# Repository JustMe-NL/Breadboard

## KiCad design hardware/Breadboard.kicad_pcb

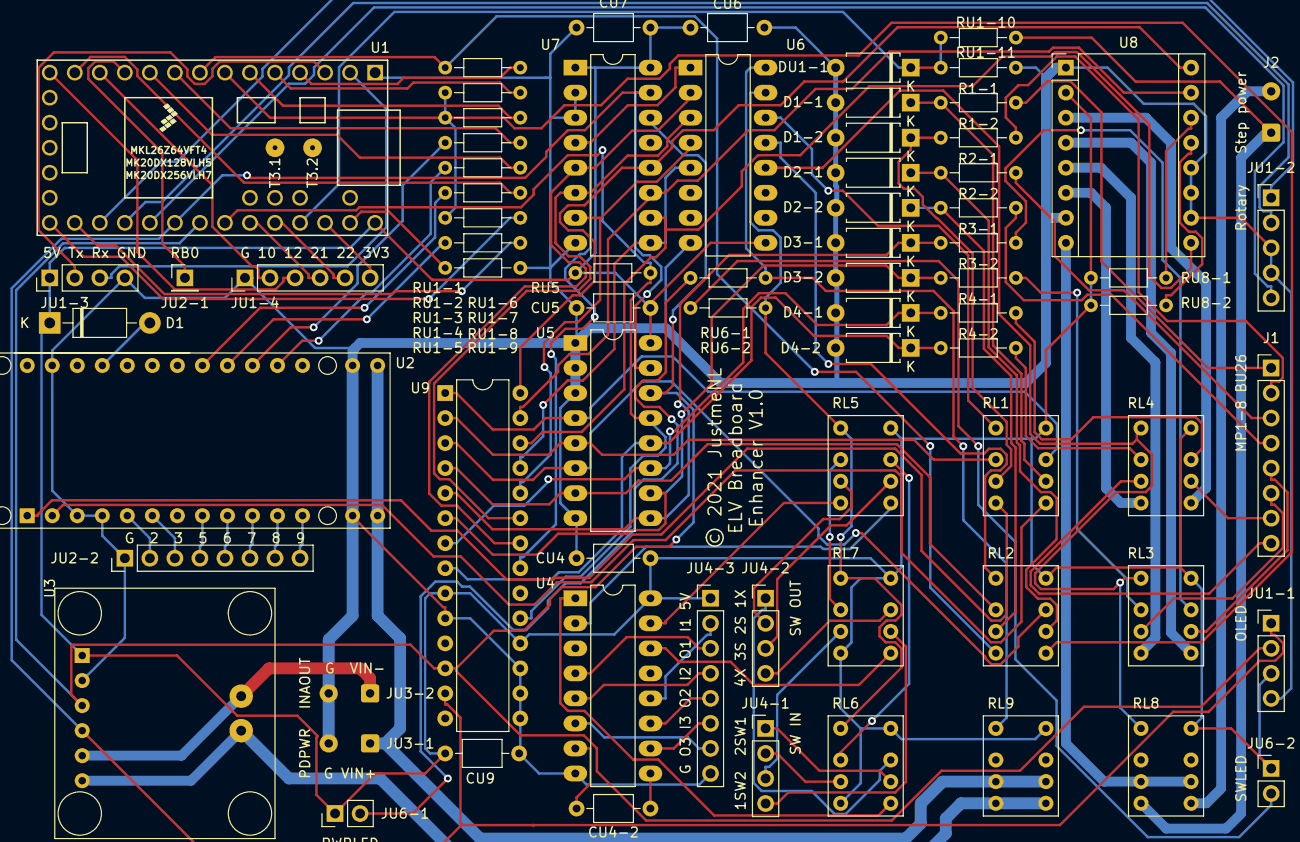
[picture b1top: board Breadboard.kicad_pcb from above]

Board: 2 copper layers, 73 parts (0 on the bottom side), 115 nets.

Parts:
CU4, CU5, CU6, CU7, CU9: C; C_Axial_L3.8mm_D2.6mm_P7.50mm_Horizontal
CU4-2: 100pF; C_Axial_L3.8mm_D2.6mm_P7.50mm_Horizontal
D1: 1N5819; D_DO-41_SOD81_P10.16mm_Horizontal
D1-1, D1-2, D2-1, D2-2, D3-1, D3-2, D4-1, D4-2: 1N4733A; D_A-405_P7.62mm_Horizontal
DU1-1: 1N4733A; D_A-405_P7.62mm_Horizontal
J1: 8PinBeardboard; PinHeader_1x08_P2.54mm_Vertical
J2: StepPower; SolderWire-0.25sqmm_1x02_P4.2mm_D0.65mm_OD1.7mm
JU1-1: OLED Display; PinHeader_1x04_P2.54mm_Vertical
JU1-2: Rotary Encoder; PinHeader_1x05_P2.54mm_Vertical
JU1-3: Serial; PinHeader_1x04_P2.54mm_Vertical
JU1-4: TeensySpare; PinHeader_1x06_P2.54mm_Vertical
JU2-1: PDSS/RB0; PinHeader_1x01_P2.54mm_Vertical
JU2-2, JU4-3: PS_Spare1; PinHeader_1x08_P2.54mm_Vertical
JU3-1: PD_Power; SolderWire-0.25sqmm_1x02_P4.2mm_D0.65mm_OD1.7mm
JU3-2: INA219; SolderWire-0.25sqmm_1x02_P4.2mm_D0.65mm_OD1.7mm
JU4-1: SW IN; PinHeader_1x04_P2.54mm_Vertical
JU4-2: SW OUT; PinHeader_1x04_P2.54mm_Vertical
JU6-1: PowerLED; PinHeader_1x02_P2.54mm_Vertical
JU6-2: SwitchLED; PinHeader_1x02_P2.54mm_Vertical
R1-1, R1-2, R2-1, R2-2, R3-1, R3-2, R4-1, R4-2: 1K; R_Axial_DIN0204_L3.6mm_D1.6mm_P7.62mm_Horizontal
RL1, RL2, RL3, RL4, RL5, RL6, RL7, RL8, RL9: HFD4-5
RU1-1, RU1-2: 2K2; R_Axial_DIN0204_L3.6mm_D1.6mm_P7.62mm_Horizontal
RU1-3: 4K7; R_Axial_DIN0204_L3.6mm_D1.6mm_P7.62mm_Horizontal
RU1-4, RU1-5, RU1-6, RU1-7, RU1-8: 100; R_Axial_DIN0204_L3.6mm_D1.6mm_P7.62mm_Horizontal
RU1-9: 0; R_Axial_DIN0204_L3.6mm_D1.6mm_P7.62mm_Horizontal
RU1-10: 10K; R_Axial_DIN0204_L3.6mm_D1.6mm_P7.62mm_Horizontal
RU1-11: 100K; R_Axial_DIN0204_L3.6mm_D1.6mm_P7.62mm_Horizontal
RU5, RU6-1, RU6-2, RU8-1, RU8-2: 1K; R_Axial_DIN0204_L3.6mm_D1.6mm_P7.62mm_Horizontal
U1: Teensy3.2; Teensy30_31_32_LC
U2: PD-Micro Module; PD_Micro
U3: INA219 Module
U4: MC14490; DIP-16_W7.62mm_LongPads
U5, U7: PCF8574; DIP-16_W7.62mm_LongPads
U6: ULN2003; DIP-16_W7.62mm_LongPads
U8: A4988 Module; Pololu_Breakout-16_15.2x20.3mm
U9: MCP23017_SP; DIP-28_W7.62mm

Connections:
+5V: CU4.1, CU5.1, CU6.1, CU7.1, CU9.1, D1.1, JU1-1.3, JU1-3.1, JU4-3.1, JU6-1.1, JU6-2.1, RL1.1, RL2.1, RL3.1, RL4.1, RL5.1, RL6.1, RL6.5, RL7.1, RL7.5, RL8.1, RL9.1, RU5.1, RU8-1.1, RU8-2.1, U1.33, U3.1, U4.16, U5.16, U6.9, U7.1, U7.16, U8.2, U9.9, U9.18
A1: RL3.4, U8.4
A2: RL3.5, U8.5
B1: RL4.4, U8.3
B2: RL4.5, U8.6
C_GPIO: U6.4, U7.7, U9.24
C_INT: RU5.2, U1.27, U5.13, U9.19
C_POWER: U6.1, U7.4, U9.21
C_SERIAL: U6.3, U7.6, U9.23
C_STEP: U6.5, U7.9, U9.25
C_SWITCH: U6.2, U7.5, U9.22
D5: RL2.4, RU1-2.1, RU1-3.1, RU1-7.1, U1.7
D6: RL2.5, RU1-1.1, U1.8
DBIN1: JU4-3.2, U4.12
DBIN2: JU4-3.4, U4.5
DBIN3: JU4-3.6, U4.10
DBOUT1: JU4-3.3, U4.4
DBOUT2: JU4-3.5, U4.11
DBOUT3: JU4-3.7, U4.6
EXP1: RL1.2, U5.4, U9.1
EXP2: RL1.7, U5.5, U9.2
EXP3: RL2.2, U5.6, U9.3
EXP4: RL2.7, U5.7, U9.4
EXP5: D3-1.1, R3-1.1, U5.9, U9.5
EXP6: D3-2.1, R3-2.1, U5.10, U9.6
EXP7: D4-1.1, R4-1.1, U5.11, U9.7
EXP8: D4-2.1, R4-2.1, U5.12, U9.8
GND: CU4.2, CU5.2, CU6.2, CU7.2, CU9.2, D1-1.2, D1-2.2, D2-1.2, D2-2.2, D3-1.2, D3-2.2, D4-1.2, D4-2.2, DU1-1.2, JU1-1.4, JU1-2.3, JU1-2.4, JU1-3.4, JU1-4.1, JU2-2.1, JU3-1.2, JU3-2.2, JU4-3.8, RU1-9.2, RU1-10.2, U1.1, U2.3, U2.4, U2.13, U2.16, U2.27, U3.2, U4.8, U5.1, U5.2, U5.3, U5.8, U6.8, U7.2, U7.3, U7.8, U8.1, U8.7, U8.10, U8.11, U8.12, U9.10, U9.15, U9.16, U9.17
unnamed: CU4-2.1, U4.9
unnamed: CU4-2.2, U4.7
unnamed: D1-1.1, R1-1.1, RL1.3
unnamed: D1-2.1, R1-2.1, RL1.6
unnamed: D1.2, U2.25
unnamed: D2-1.1, R2-1.1, RL2.3
unnamed: D2-2.1, R2-2.1, RL2.6
unnamed: DU1-1.1, RU1-10.1, RU1-11.2, U1.30
unnamed: J1.1, R1-1.2
unnamed: J1.2, R1-2.2
unnamed: J1.3, R2-1.2
unnamed: J1.4, R2-2.2
unnamed: J1.5, RL3.3
unnamed: J1.6, RL3.6
unnamed: J1.7, RL4.3
unnamed: J1.8, RL4.6
unnamed: J2.2, RL8.4
unnamed: JU1-4.6, U1.31
unnamed: JU2-2.2, U2.5
unnamed: JU2-2.3, U2.6
unnamed: JU2-2.4, U2.8
unnamed: JU2-2.5, U2.9
unnamed: JU2-2.6, U2.10
unnamed: JU2-2.7, U2.11
unnamed: JU2-2.8, U2.12
unnamed: JU3-2.1, U3.5, U3.7
unnamed: JU4-1.1, RL6.3
unnamed: JU4-1.2, RL6.6
unnamed: JU4-1.3, RL7.6
unnamed: JU4-1.4, RL7.3
unnamed: JU4-2.1, RL6.2
unnamed: JU4-2.2, RL5.6
unnamed: JU4-2.3, RL5.3
unnamed: JU4-2.4, RL7.2
unnamed: JU6-1.2, RU6-1.1
unnamed: JU6-2.2, RU6-2.1
unnamed: R3-1.2, RL3.2
unnamed: R3-2.2, RL3.7
unnamed: R4-1.2, RL4.2
unnamed: R4-2.2, RL4.7
unnamed: RL5.2, RL6.7
unnamed: RL5.4, U4.2
unnamed: RL5.5, U4.15
unnamed: RL5.7, RL7.7
unnamed: RL6.4, U4.1
unnamed: RL7.4, U4.14
unnamed: RL9.4, RL9.5, U3.6, U3.8
unnamed: RU1-1.2, U1.4
unnamed: RU1-2.2, U1.5
unnamed: RU1-3.2, U1.6
unnamed: RU1-4.1, U2.19
unnamed: RU1-4.2, U1.9
unnamed: RU1-5.1, U2.18
unnamed: RU1-5.2, U1.10
unnamed: RU1-6.1, U2.21
unnamed: RU1-6.2, U1.13
unnamed: RU1-7.2, U1.20
unnamed: RU1-8.1, U2.20
unnamed: RU1-8.2, U1.21
unnamed: RU1-9.1, U1.32
unnamed: RU8-1.2, U8.14
unnamed: RU8-2.2, U8.13
PDSS_RB0: JU2-1.1, U1.11
PD_POWER: JU3-1.1, RL9.3, RL9.6, U2.14, U2.15
ROTA: JU1-2.1, U1.22
ROTB: JU1-2.2, U1.23
ROTSW: JU1-2.5, U1.24
RX: RL1.4, U2.2
R_GPIO: RL2.8, U6.13
R_POWER: RL9.8, RU6-1.2, U6.16
R_SERIAL: RL1.8, U6.14
R_STEP: RL3.8, RL4.8, RL8.8, U6.12
R_SWITCH: RL5.8, RL6.8, RL7.8, RU6-2.2, U6.15
SCL: JU1-1.2, U1.26, U3.3, U5.14, U7.14, U9.12
SDA: JU1-1.1, U1.25, U3.4, U5.15, U7.15, U9.13
S_DIR: U7.12, U8.16, U9.28
S_PWR: RL8.3, RL8.6, U8.8
S_SLEEP: U7.10, U8.9, U9.26
S_STEP: U7.11, U8.15, U9.27
TNC1: JU1-4.2, U1.12
TNC2: JU1-4.3, U1.14
TNC3: JU1-4.4, U1.28
TNC4: JU1-4.5, U1.29
TRX: JU1-3.3, U1.2
TTX: JU1-3.2, U1.3
TX: RL1.5, U2.1
vsense: J2.1, RL8.5, RU1-11.1

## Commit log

2021-03-31 fix branching
2021-04-15 Bugfixes, prepare for 4066
2021-04-23 bugfixes & 4066 functionality
2021-04-29 Updated SPI protocol
2021-05-05 Added DMA I2C Monitor
2021-05-23 Cleanup main & interrupt driven I2C monitor
2021-05-29 Interruot monitor, cleanup loops, fix logicblocks

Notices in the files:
hardware/Breadboard.kicad_pcb:
© 2021 JustmeNL
